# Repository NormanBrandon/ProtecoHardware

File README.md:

# ProtecoHardware
Repositorio Provisional del Proyecto de La sección de Hardware

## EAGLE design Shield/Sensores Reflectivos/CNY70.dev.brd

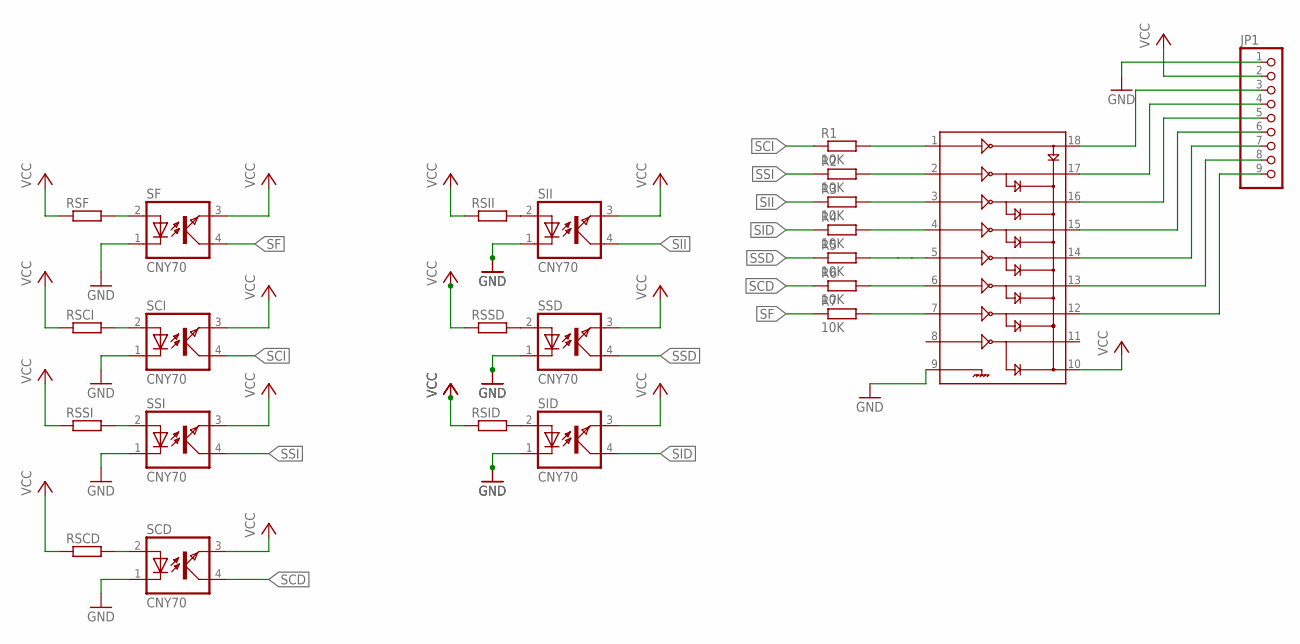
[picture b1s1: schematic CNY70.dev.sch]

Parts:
JP1: PINHD-1X9/90; 1X09/90
R1, R2, R3, R4, R5, R6, R7: 10K; R1206
RSCD: R-EU_R1206; R1206
RSCI: R-EU_R1206; R1206
RSF: R-EU_R1206; R1206
RSID: R-EU_R1206; R1206
RSII: R-EU_R1206; R1206
RSSD: R-EU_R1206; R1206
RSSI: R-EU_R1206; R1206
SCD: CNY70
SCI: CNY70
SF: CNY70
SID: CNY70
SII: CNY70
SSD: CNY70
SSI: CNY70
ULN1: ULN2803; DIL18

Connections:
GND: JP1.1, SCD.1, SCI.1, SF.1, SID.1, SII.1, SSD.1, SSI.1, ULN1.9
unnamed: RSII.2, SII.2
unnamed: RSSD.2, SSD.2
unnamed: RSID.2, SID.2
unnamed: JP1.3, ULN1.18
unnamed: RSCD.2, SCD.2
unnamed: RSSI.2, SSI.2
unnamed: RSCI.2, SCI.2
unnamed: RSF.2, SF.2
unnamed: JP1.4, ULN1.17
unnamed: JP1.5, ULN1.16
unnamed: JP1.6, ULN1.15
unnamed: JP1.7, ULN1.14
unnamed: JP1.8, ULN1.13
unnamed: JP1.9, ULN1.12
unnamed: R1.2, ULN1.1
unnamed: R2.2, ULN1.2
unnamed: R3.2, ULN1.3
unnamed: R4.2, ULN1.4
unnamed: R5.2, ULN1.5
unnamed: R6.2, ULN1.6
unnamed: R7.2, ULN1.7
SCD: R6.1, SCD.4
SCI: R1.1, SCI.4
SF: R7.1, SF.4
SID: R4.1, SID.4
SII: R3.1, SII.4
SSD: R5.1, SSD.4
SSI: R2.1, SSI.4
VCC: JP1.2, RSCD.1, RSCI.1, RSF.1, RSID.1, RSII.1, RSSD.1, RSSI.1, SCD.3, SCI.3, SF.3, SID.3, SII.3, SSD.3, SSI.3, ULN1.10

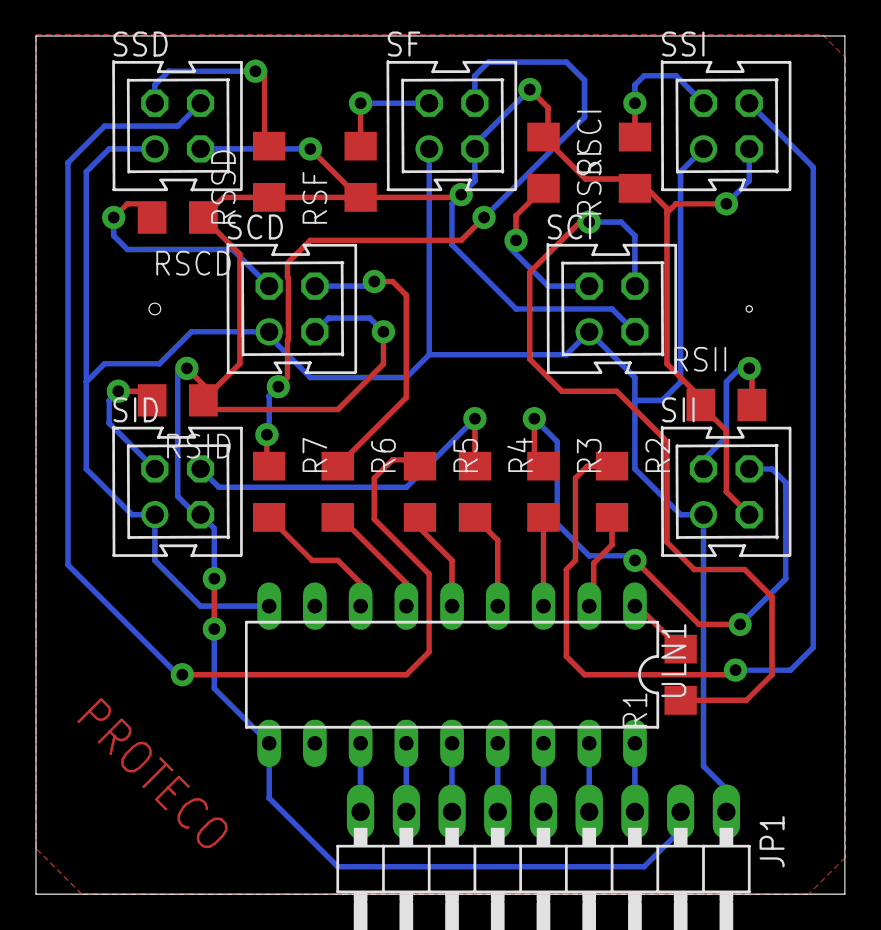
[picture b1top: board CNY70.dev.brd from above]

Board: 2 copper layers, 44.9 x 47.7 mm, 23 parts (0 on the bottom side), 30 nets.

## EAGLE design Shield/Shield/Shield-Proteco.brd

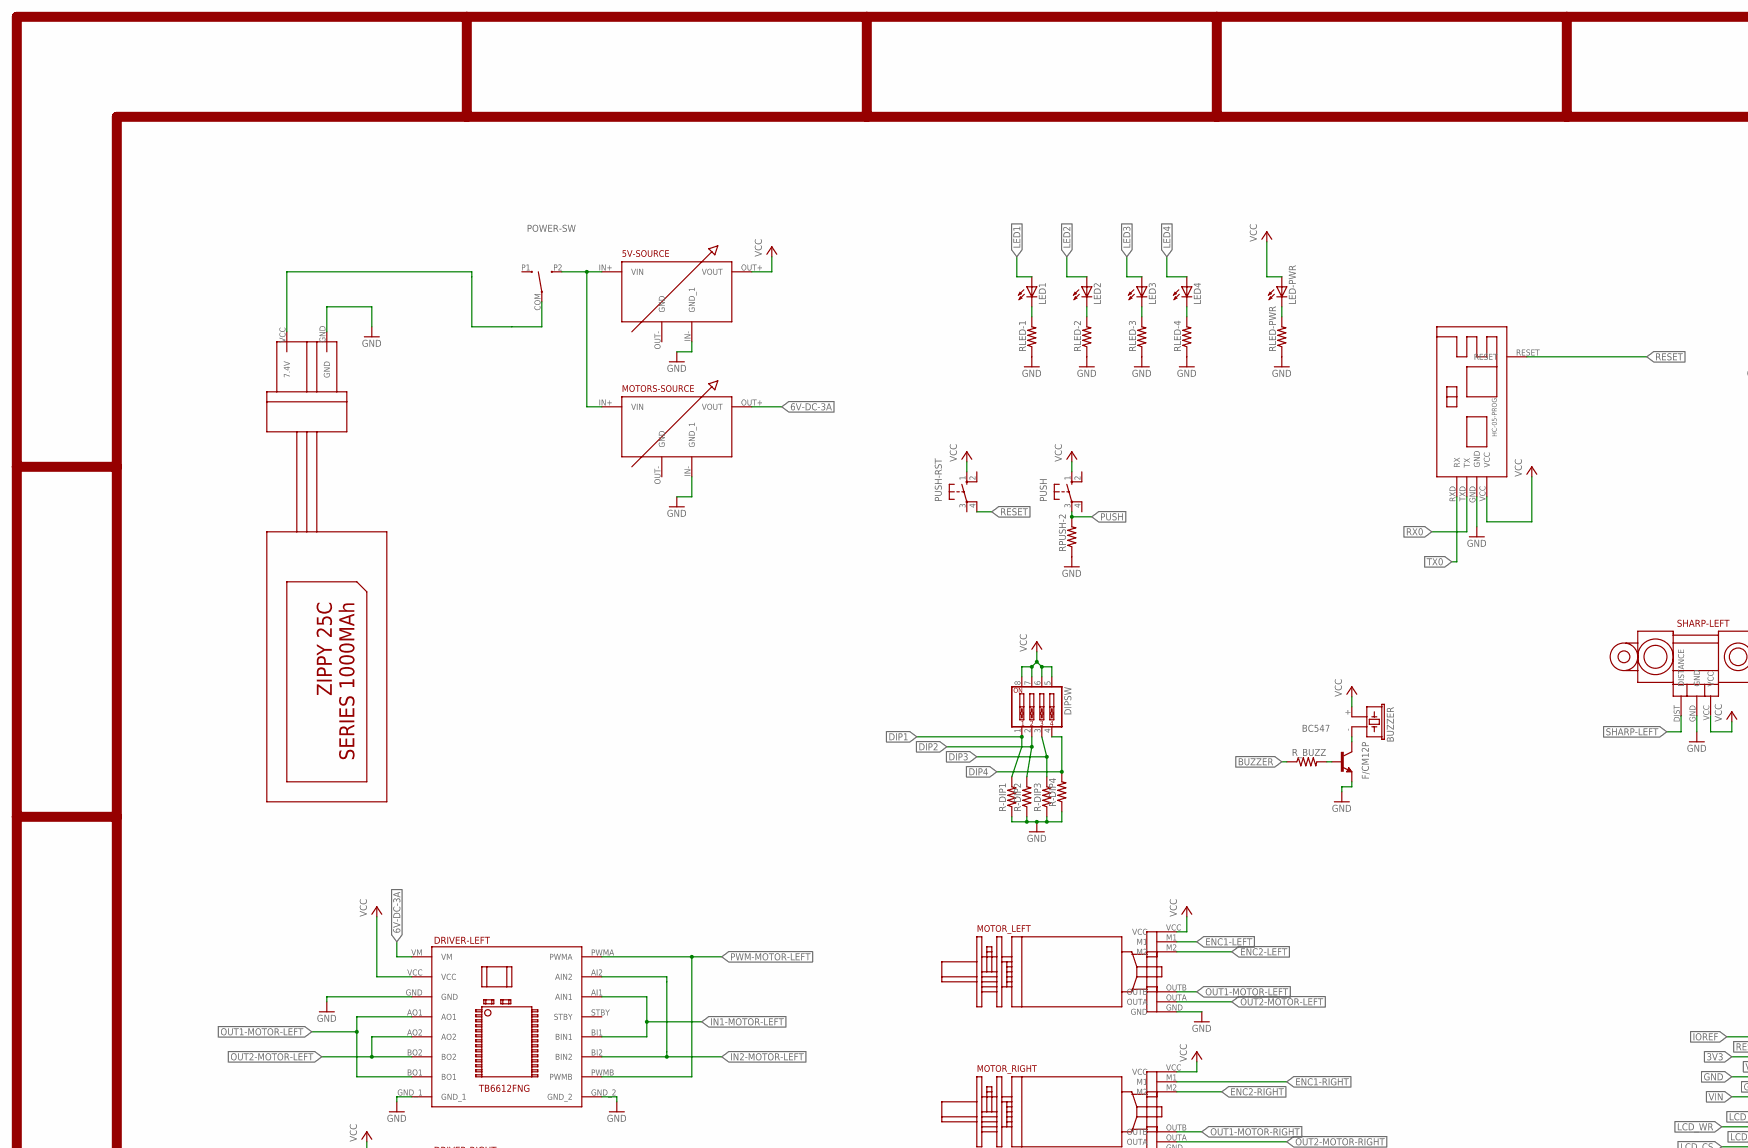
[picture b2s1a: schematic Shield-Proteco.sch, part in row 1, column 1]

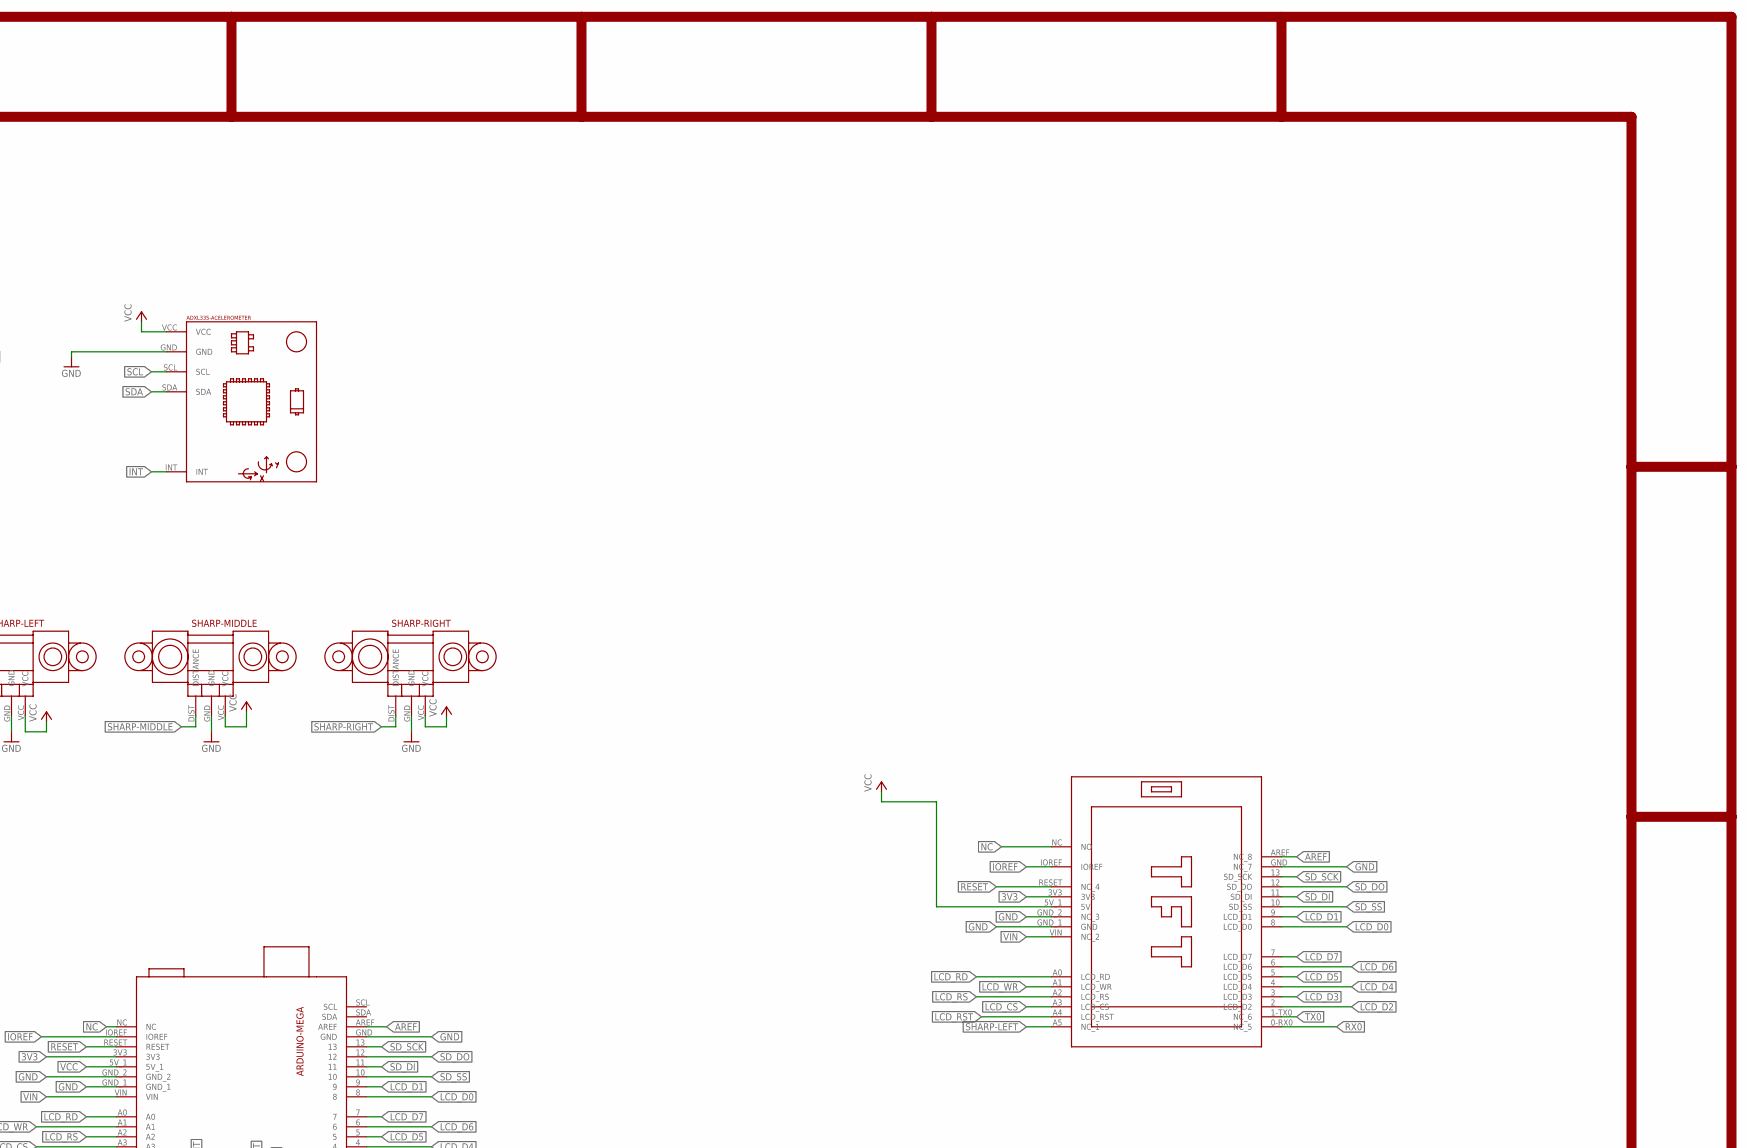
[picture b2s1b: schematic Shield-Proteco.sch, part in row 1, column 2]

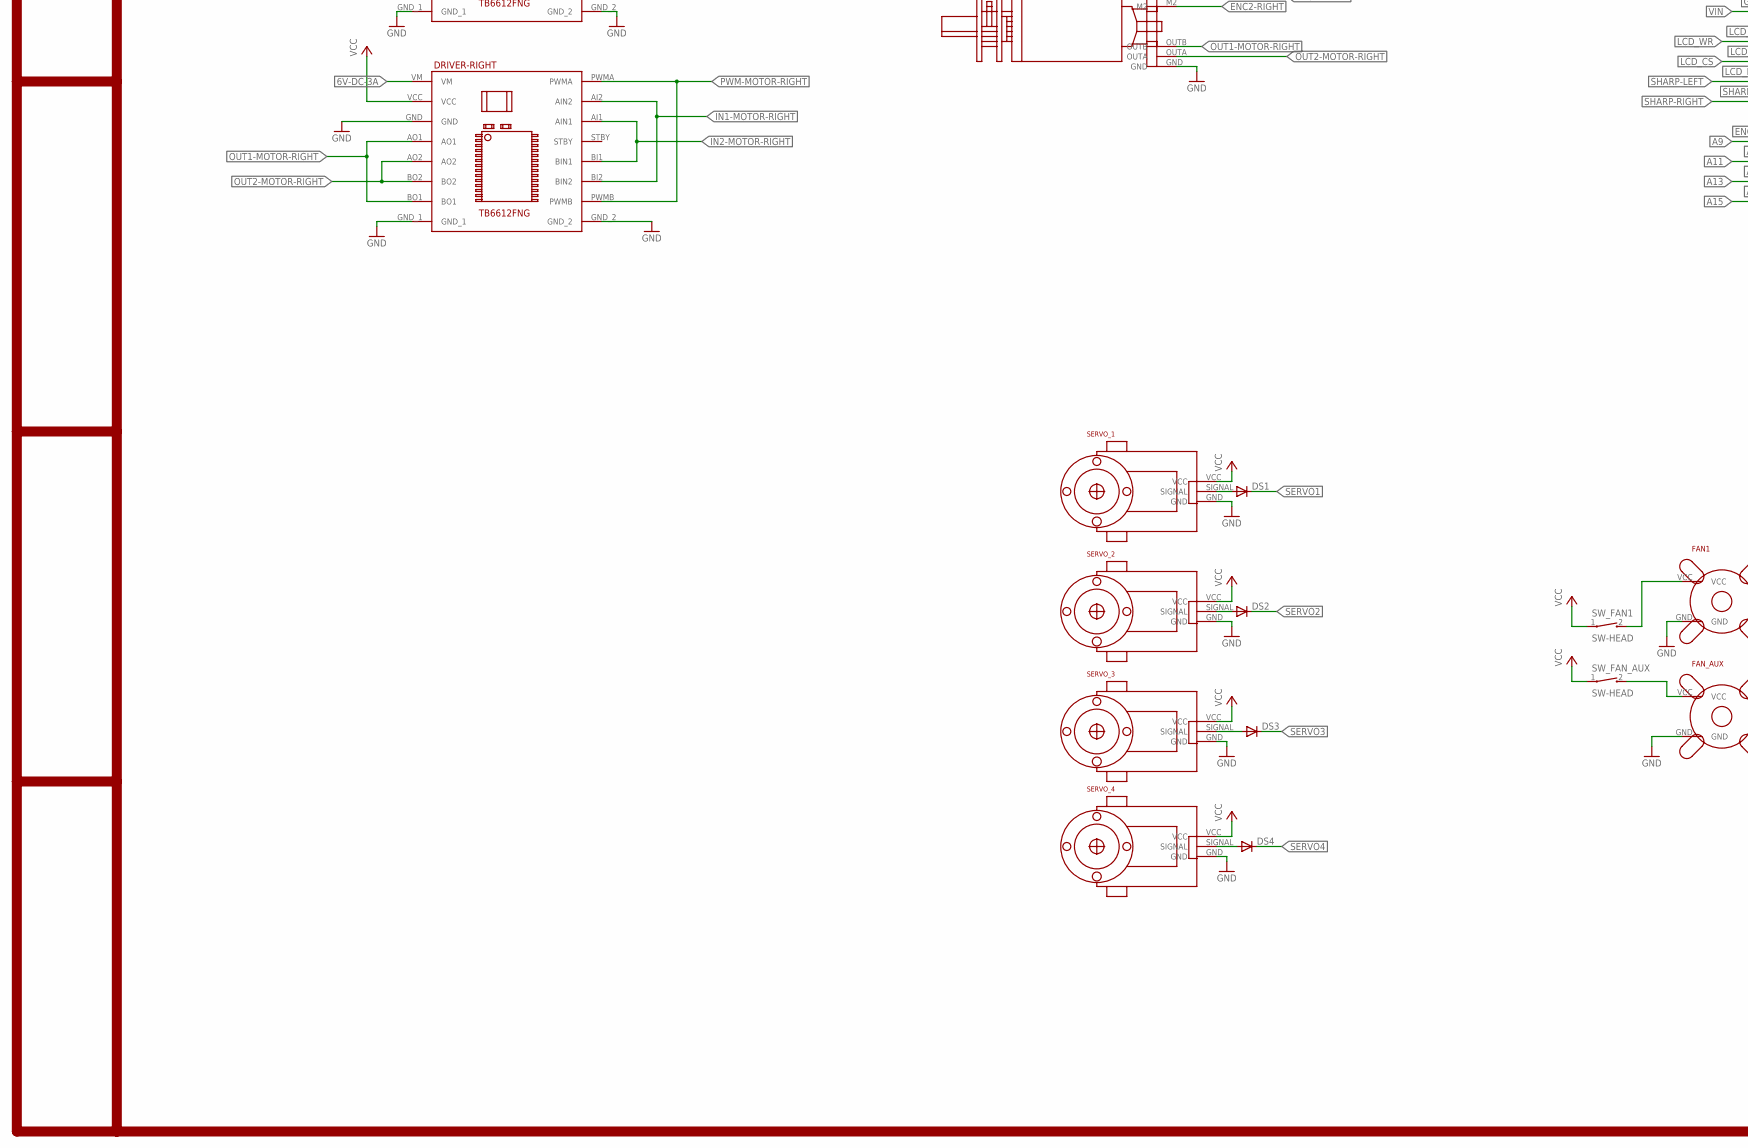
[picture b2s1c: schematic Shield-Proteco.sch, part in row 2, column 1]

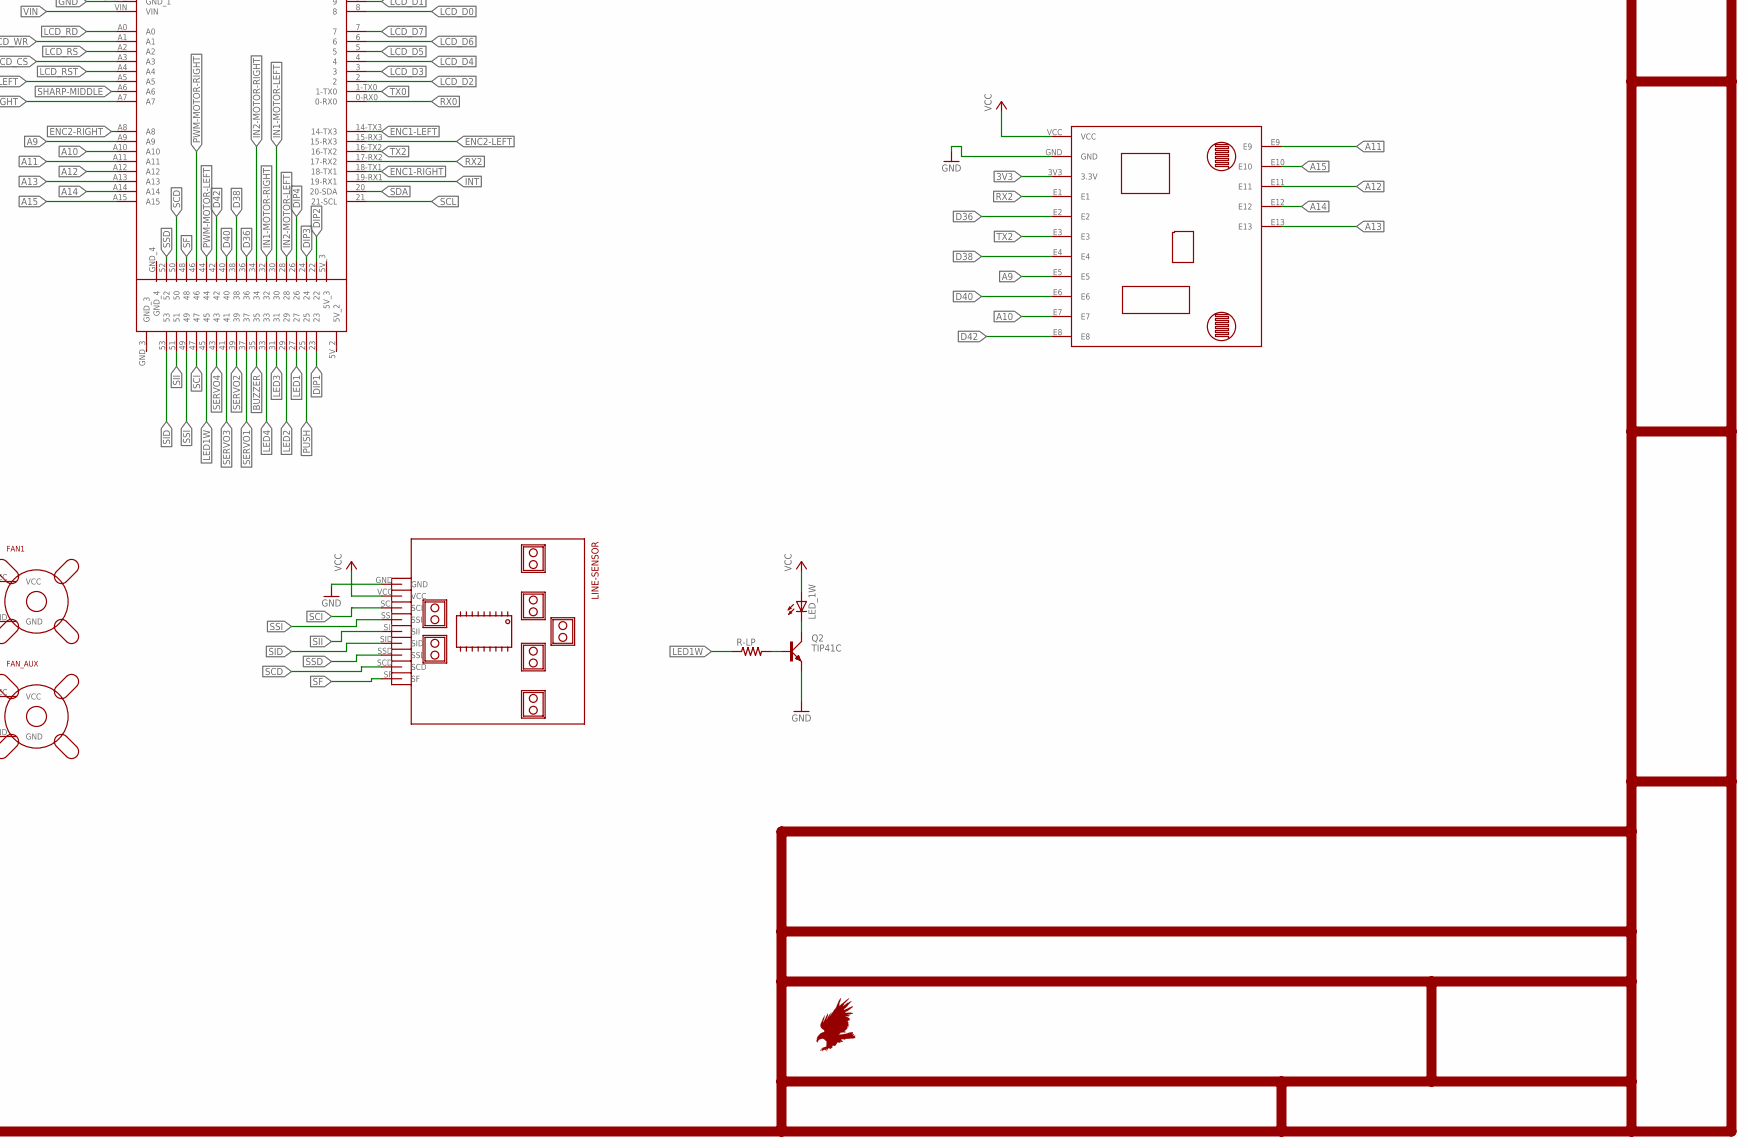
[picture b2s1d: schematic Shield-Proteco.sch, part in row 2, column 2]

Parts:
5V-SOURCE: STEPDOWN-DC-DC
ADXL335-ACELEROMETER: ACELEROMETER-JST-5; ACELEROMETER-MPU6050-JST-5
ARDUINO-MEGA: ARDUINO_MEGA; ARDUINO-MEGA
BC547: BC547-NPN-TO92-CBE; TO92-CBE
BUZZER: F/CM12P
DIPSW: SW_DIP-4; EDG-04
DRIVER-LEFT: TB6612FNG
DRIVER-RIGHT: TB6612FNG
DS1, DS2, DS3, DS4: DIODE-DO-214AC; DO-214AC
FAN1: FAN-MOLEX; 1X02
FAN_AUX: FAN-MOLEX; 1X02
HC-05-PROG: HC-05-PROGRAMER; HC-05-PROG-COMP
LED1, LED2, LED3, LED4: LEDCHIPLED_1206; CHIPLED_1206
LED-PWR: LEDCHIPLED_1206; CHIPLED_1206
LED_1W: LED-1W-3V3; 1X02
LINE-SENSOR: CNY70-ARRAY-HEADER
MOTORS-SOURCE: STEPDOWN-DC-DC
MOTOR_LEFT: POLOLU-MICROMOTOR; JST
MOTOR_RIGHT: POLOLU-MICROMOTOR; JST
POWER-SW: SLIDE-3
PUSH: 10-XX; B3F-10XX
PUSH-RST: 10-XX; B3F-10XX
Q2: TIP41C; TO220AV
R-DIP1, R-DIP2, R-DIP3, R-DIP4: R-US_M1206; M1206
R-LP: R-US_M1206; M1206
RLED-1, RLED-2, RLED-3, RLED-4: R-US_M1206; M1206
RLED-PWR: R-US_M1206; M1206
RPUSH-2: R-US_M1206; M1206
R_BUZZ: R-US_M1206; M1206
SERVO_1, SERVO_2, SERVO_3, SERVO_4: SERVOMOTORES; SERVO
SHARP-LEFT: SHARP
SHARP-MIDDLE: SHARP
SHARP-RIGHT: SHARP
SW_FAN1: SW-HEAD; 1X02
SW_FAN_AUX: SW-HEAD; 1X02
U$9: SENSOR-MISCELANEOUS
U$14: TFT_ARDUINO-UNO-MEGA; TFT-ARDUINO-UNO-MEGA
U$23: ZIIPY-7.4V; XT60

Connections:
3V3: ARDUINO-MEGA.3V3, U$9.3V3 (3.3V), U$14.3V3
6V-DC-3A: DRIVER-LEFT.VM, DRIVER-RIGHT.VM, MOTORS-SOURCE.OUT+ (VOUT)
A9: ARDUINO-MEGA.A9, U$9.E5
A10: ARDUINO-MEGA.A10, U$9.E7
A11: ARDUINO-MEGA.A11, U$9.E9
A12: ARDUINO-MEGA.A12, U$9.E11
A13: ARDUINO-MEGA.A13, U$9.E13
A14: ARDUINO-MEGA.A14, U$9.E12
A15: ARDUINO-MEGA.A15, U$9.E10
AREF: ARDUINO-MEGA.AREF, U$14.AREF (NC_8)
BUZZER: ARDUINO-MEGA.35, R_BUZZ.1
D36: ARDUINO-MEGA.36, U$9.E2
D38: ARDUINO-MEGA.38, U$9.E4
D40: ARDUINO-MEGA.40, U$9.E6
D42: ARDUINO-MEGA.42, U$9.E8
DIP1: ARDUINO-MEGA.23, DIPSW.1, R-DIP1.2
DIP2: ARDUINO-MEGA.22, DIPSW.2, R-DIP2.2
ENC1-LEFT: ARDUINO-MEGA.14-TX3, MOTOR_LEFT.M1
ENC1-RIGHT: ARDUINO-MEGA.18-TX1, MOTOR_RIGHT.M1
ENC2-LEFT: ARDUINO-MEGA.15-RX3, MOTOR_LEFT.M2
ENC2-RIGHT: ARDUINO-MEGA.A8, MOTOR_RIGHT.M2
GND: 5V-SOURCE.IN- (GND_1), ADXL335-ACELEROMETER.GND, ARDUINO-MEGA.GND, ARDUINO-MEGA.GND_1, ARDUINO-MEGA.GND_2, BC547.E, DRIVER-LEFT.GND, DRIVER-LEFT.GND_1, DRIVER-LEFT.GND_2, DRIVER-RIGHT.GND, DRIVER-RIGHT.GND_1, DRIVER-RIGHT.GND_2, FAN1.GND, FAN_AUX.GND, HC-05-PROG.GND, LINE-SENSOR.GND, MOTORS-SOURCE.IN- (GND_1), MOTOR_LEFT.GND, MOTOR_RIGHT.GND, Q2.E, R-DIP1.1, R-DIP2.1, R-DIP3.1, R-DIP4.1, RLED-1.1, RLED-2.1, RLED-3.1, RLED-4.1, RLED-PWR.1, RPUSH-2.1, SERVO_1.GND, SERVO_2.GND, SERVO_3.GND, SERVO_4.GND, SHARP-LEFT.GND, SHARP-MIDDLE.GND, SHARP-RIGHT.GND, U$9.GND, U$14.GND (NC_7), U$14.GND_1 (GND), U$14.GND_2 (NC_3), U$23.GND; also elsewhere on the board
IN1-MOTOR-LEFT: ARDUINO-MEGA.30, DRIVER-LEFT.AI1 (AIN1), DRIVER-LEFT.BI1 (BIN1)
IN1-MOTOR-RIGHT: ARDUINO-MEGA.32, DRIVER-RIGHT.AI2 (AIN2), DRIVER-RIGHT.BI2 (BIN2)
IN2-MOTOR-LEFT: ARDUINO-MEGA.28, DRIVER-LEFT.AI2 (AIN2), DRIVER-LEFT.BI2 (BIN2)
IN2-MOTOR-RIGHT: ARDUINO-MEGA.34, DRIVER-RIGHT.AI1 (AIN1), DRIVER-RIGHT.BI1 (BIN1)
INT: ADXL335-ACELEROMETER.INT, ARDUINO-MEGA.19-RX1
IOREF: ARDUINO-MEGA.IOREF, U$14.IOREF
LCD_CS: ARDUINO-MEGA.A3, U$14.A3 (LCD_CS)
LCD_D0: ARDUINO-MEGA.8, U$14.8 (LCD_D0)
LCD_D1: ARDUINO-MEGA.9, U$14.9 (LCD_D1)
LCD_D2: ARDUINO-MEGA.2, U$14.2 (LCD_D2)
LCD_D3: ARDUINO-MEGA.3, U$14.3 (LCD_D3)
LCD_D4: ARDUINO-MEGA.4, U$14.4 (LCD_D4)
LCD_D5: ARDUINO-MEGA.5, U$14.5 (LCD_D5)
LCD_D6: ARDUINO-MEGA.6, U$14.6 (LCD_D6)
LCD_D7: ARDUINO-MEGA.7, U$14.7 (LCD_D7)
LCD_RD: ARDUINO-MEGA.A0, U$14.A0 (LCD_RD)
LCD_RS: ARDUINO-MEGA.A2, U$14.A2 (LCD_RS)
LCD_RST: ARDUINO-MEGA.A4, U$14.A4 (LCD_RST)
LCD_WR: ARDUINO-MEGA.A1, U$14.A1 (LCD_WR)
LED1: ARDUINO-MEGA.27, LED1.A
LED1W: ARDUINO-MEGA.45, R-LP.1
LED2: ARDUINO-MEGA.29, LED2.A
LED3: ARDUINO-MEGA.31, LED3.A
LED4: ARDUINO-MEGA.33, LED4.A
unnamed: LED_1W.2 (C), Q2.C
unnamed: Q2.B, R-LP.2
unnamed: BC547.C, BUZZER.- (2)
unnamed: BC547.B, R_BUZZ.2
unnamed: FAN_AUX.VCC, SW_FAN_AUX.2
unnamed: LED1.C, RLED-1.2
unnamed: LED2.C, RLED-2.2
unnamed: LED3.C, RLED-3.2
unnamed: LED4.C, RLED-4.2
unnamed: DS4.A, SERVO_4.SIGNAL
unnamed: DS3.A, SERVO_3.SIGNAL
unnamed: DS2.A, SERVO_2.SIGNAL
unnamed: LED-PWR.C, RLED-PWR.2
unnamed: DS1.A, SERVO_1.SIGNAL
unnamed: FAN1.VCC, SW_FAN1.2
unnamed 102: POWER-SW.COM, U$23.VCC (7.4V); also elsewhere on the board
NC: ARDUINO-MEGA.NC, U$14.NC (NO)
OUT1-MOTOR-LEFT: DRIVER-LEFT.AO1, DRIVER-LEFT.BO1, MOTOR_LEFT.OUTB
OUT1-MOTOR-RIGHT: DRIVER-RIGHT.AO1, DRIVER-RIGHT.BO1, MOTOR_RIGHT.OUTB
OUT2-MOTOR-LEFT: DRIVER-LEFT.AO2, DRIVER-LEFT.BO2, MOTOR_LEFT.OUTA
OUT2-MOTOR-RIGHT: DRIVER-RIGHT.AO2, DRIVER-RIGHT.BO2, MOTOR_RIGHT.OUTA
PUSH: ARDUINO-MEGA.25, PUSH.3, RPUSH-2.2
PWM-MOTOR-LEFT: ARDUINO-MEGA.44, DRIVER-LEFT.PWMA, DRIVER-LEFT.PWMB
PWM-MOTOR-RIGHT: ARDUINO-MEGA.46, DRIVER-RIGHT.PWMA, DRIVER-RIGHT.PWMB
RESET: ARDUINO-MEGA.RESET, HC-05-PROG.RESET, PUSH-RST.4 (P1), U$14.RESET (NC_4)
RX0: ARDUINO-MEGA.0-RX0, HC-05-PROG.TXD (TX), U$14.0-RX0 (NC_5)
RX2: ARDUINO-MEGA.17-RX2, U$9.E1
SCD: ARDUINO-MEGA.50, LINE-SENSOR.SCD
SCI: ARDUINO-MEGA.47, LINE-SENSOR.SCI
SCL: ADXL335-ACELEROMETER.SCL, ARDUINO-MEGA.21 (21-SCL)
SDA: ADXL335-ACELEROMETER.SDA, ARDUINO-MEGA.20 (20-SDA)
SD_DI: ARDUINO-MEGA.11, U$14.11 (SD_DI)
SD_DO: ARDUINO-MEGA.12, U$14.12 (SD_DO)
SD_SCK: ARDUINO-MEGA.13, U$14.13 (SD_SCK)
SD_SS: ARDUINO-MEGA.10, U$14.10 (SD_SS)
SERVO1: ARDUINO-MEGA.37, DS1.C
SERVO2: ARDUINO-MEGA.39, DS2.C
SERVO3: ARDUINO-MEGA.41, DS3.C
SERVO4: ARDUINO-MEGA.43, DS4.C
SF: ARDUINO-MEGA.48, LINE-SENSOR.SF
SHARP-LEFT: ARDUINO-MEGA.A5, SHARP-LEFT.DIST (DISTANCE), U$14.A5 (NC_1)
SHARP-MIDDLE: ARDUINO-MEGA.A6, SHARP-MIDDLE.DIST (DISTANCE)
SHARP-RIGHT: ARDUINO-MEGA.A7, SHARP-RIGHT.DIST (DISTANCE)
SID: ARDUINO-MEGA.53, LINE-SENSOR.SID
SII: ARDUINO-MEGA.51, LINE-SENSOR.SII
SSD: ARDUINO-MEGA.52, LINE-SENSOR.SSD
SSI: ARDUINO-MEGA.49, LINE-SENSOR.SSI
TX0: ARDUINO-MEGA.1-TX0, HC-05-PROG.RXD (RX), U$14.1-TX0 (NC_6)
TX2: ARDUINO-MEGA.16-TX2, U$9.E3
VCC: 5V-SOURCE.OUT+ (VOUT), ADXL335-ACELEROMETER.VCC, ARDUINO-MEGA.5V_1, BUZZER.+ (1), DIPSW.5, DIPSW.6, DIPSW.7, DIPSW.8, DRIVER-LEFT.STBY, DRIVER-LEFT.VCC, DRIVER-RIGHT.STBY, DRIVER-RIGHT.VCC, HC-05-PROG.VCC, LED-PWR.A, LED_1W.1 (A), LINE-SENSOR.VCC, MOTOR_LEFT.VCC, MOTOR_RIGHT.VCC, PUSH.1 (S), PUSH-RST.1 (S), SERVO_1.VCC, SERVO_2.VCC, SERVO_3.VCC, SERVO_4.VCC, SHARP-LEFT.VCC, SHARP-MIDDLE.VCC, SHARP-RIGHT.VCC, SW_FAN1.1, SW_FAN_AUX.1, U$9.VCC, U$14.5V_1 (5V); also elsewhere on the board

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
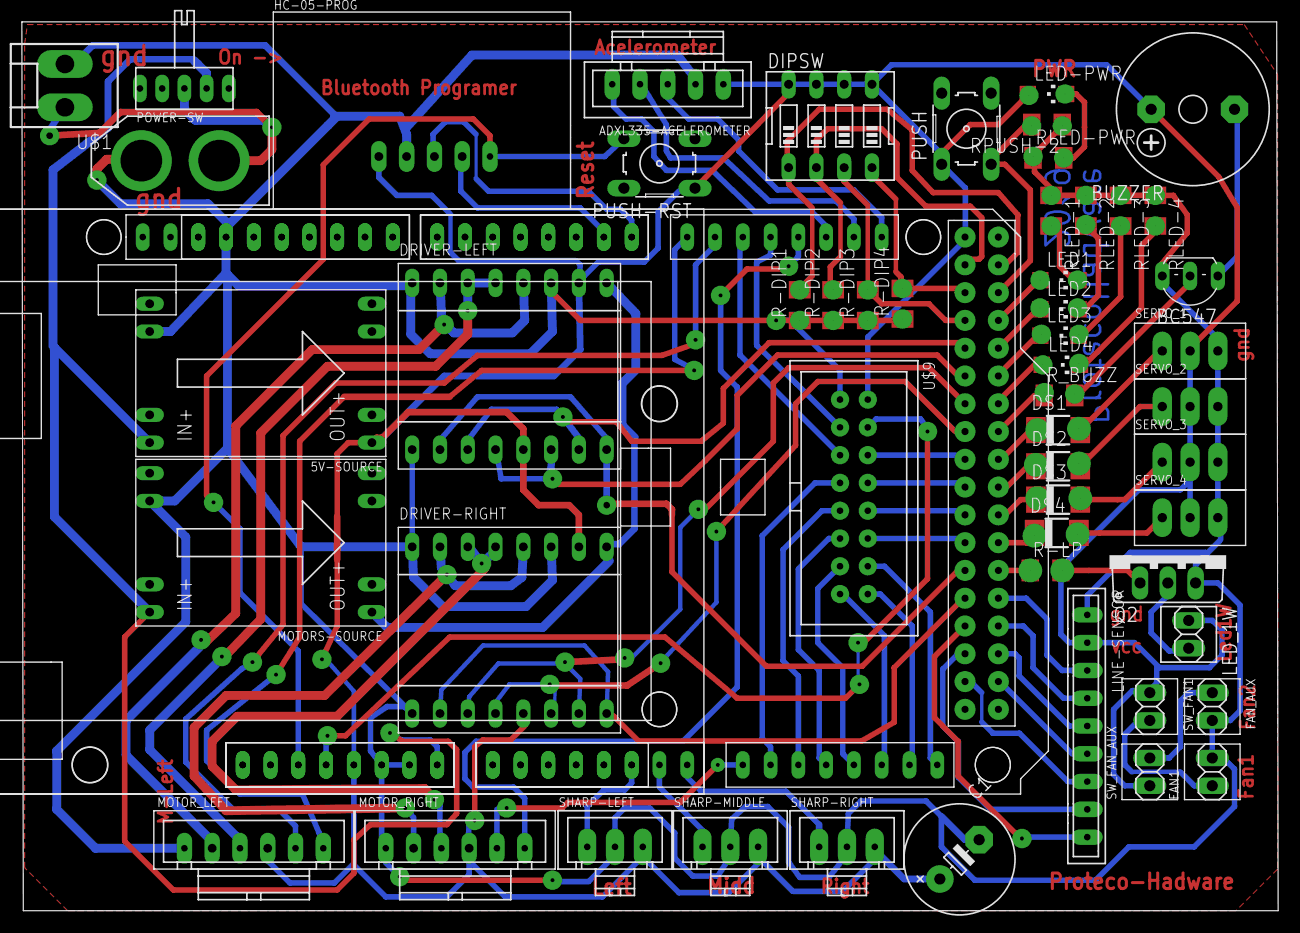
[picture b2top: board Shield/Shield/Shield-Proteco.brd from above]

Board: 2 copper layers, 114.9 x 81.3 mm, 55 parts (0 on the bottom side), 99 nets.

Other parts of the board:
C1: E5-10,5
U$1: LIPO7.4MOLEX; KK-156-2

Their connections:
GND: C1.-, U$1.GND; also elsewhere on the board
unnamed 102: U$1.VCC; also elsewhere on the board
VCC: C1.+; also elsewhere on the board

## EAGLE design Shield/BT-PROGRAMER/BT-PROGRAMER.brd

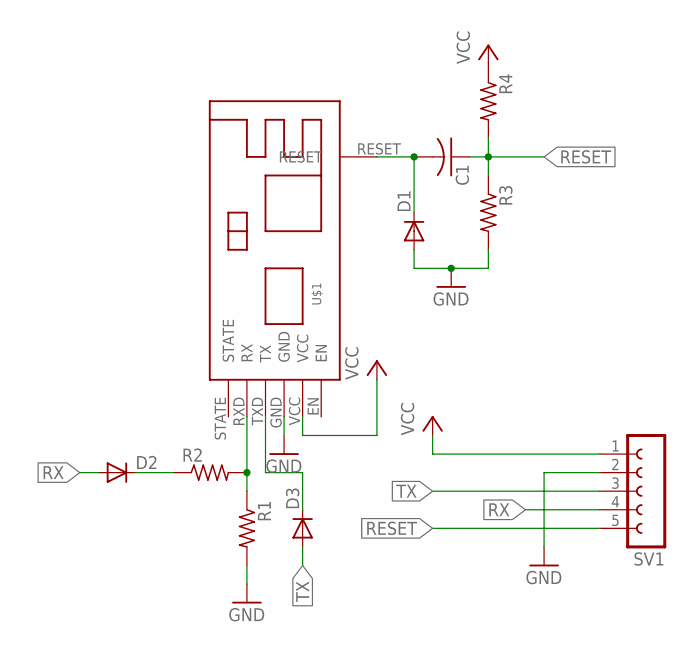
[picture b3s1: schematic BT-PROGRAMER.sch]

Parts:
C1: C-USC0603; C0603
D1, D2, D3: DIODE-DO-214AC; DO-214AC
R1, R2, R3, R4: R-US_M1206; M1206
SV1: FE05-1
U$1: HC-05-PROG

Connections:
GND: D1.A, R1.2, R3.2, SV1.2, U$1.GND
unnamed: R1.1, R2.2, U$1.RXD (RX)
unnamed: C1.2, D1.C, U$1.RESET
unnamed: D2.C, R2.1
unnamed: D3.C, U$1.TXD (TX)
RESET: C1.1, R3.1, R4.2, SV1.5
RX: D2.A, SV1.4
TX: D3.A, SV1.3
VCC: R4.1, SV1.1, U$1.VCC

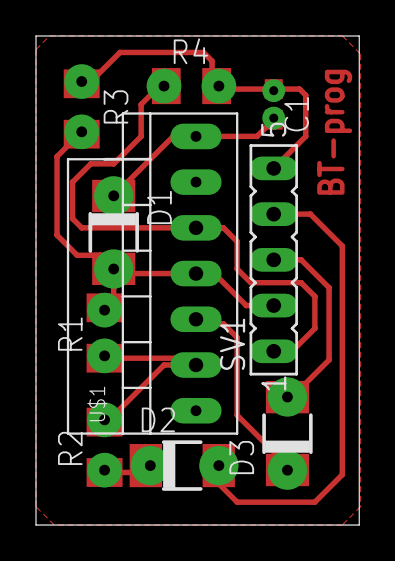
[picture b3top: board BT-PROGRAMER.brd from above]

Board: 2 copper layers, 18.0 x 27.2 mm, 10 parts (0 on the bottom side), 9 nets.

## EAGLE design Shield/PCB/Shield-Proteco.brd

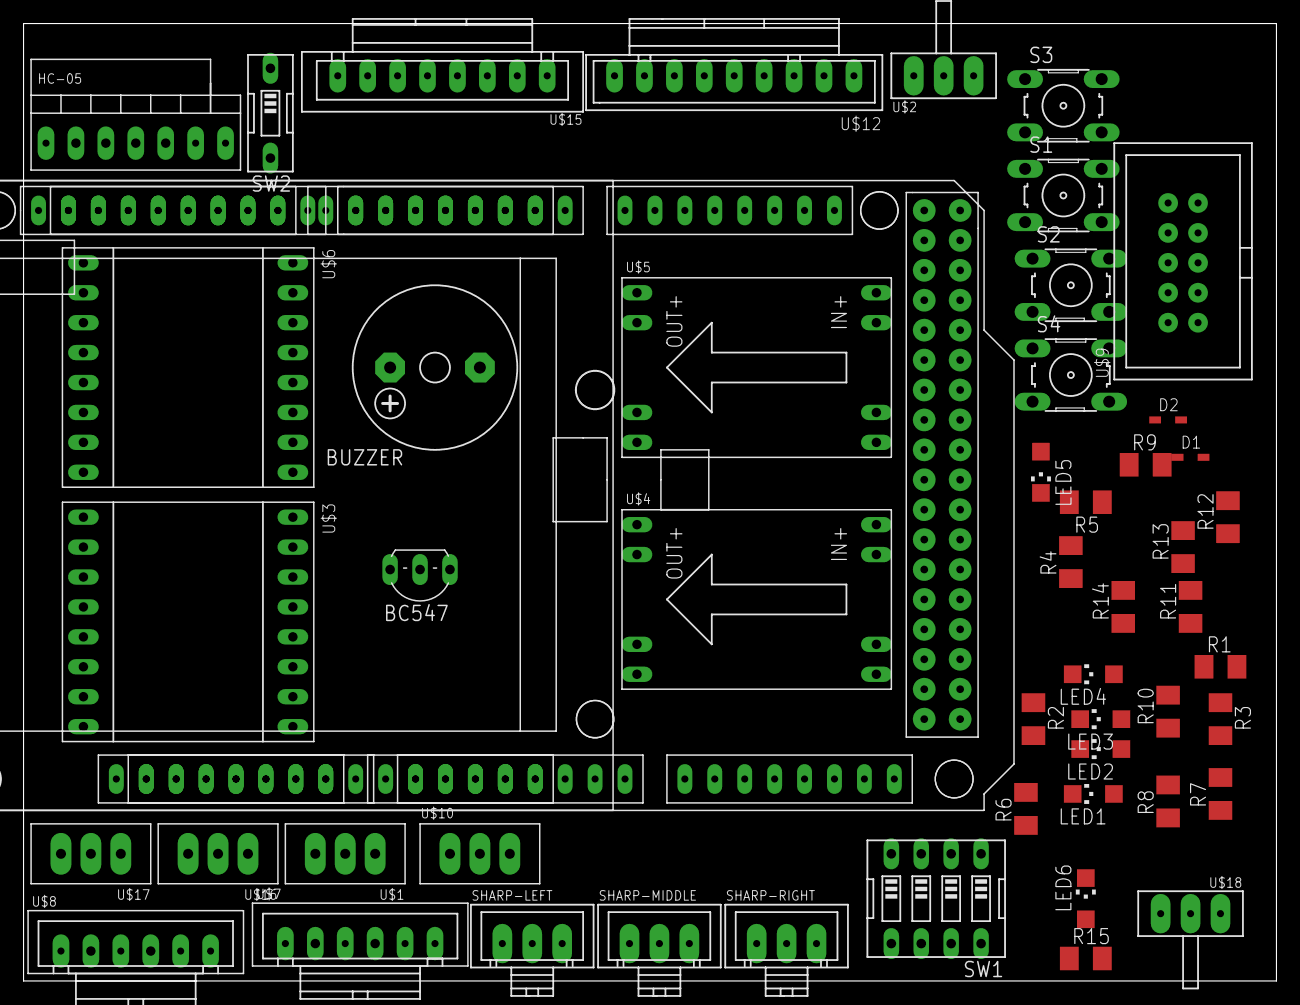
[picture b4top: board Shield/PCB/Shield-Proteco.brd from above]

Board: 2 copper layers, 106.3 x 81.3 mm, 52 parts (0 on the bottom side), 37 nets, no tracks yet.

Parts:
ARDUINO-MEGA: ARDUINO_MEGA; ARDUINO-MEGA
BC547: TO92-CBE
BUZZER: F/CM12P
D1, D2: SOD323
HC-05: HC-05-PROG
LED1, LED2, LED3, LED4, LED5, LED6: CHIPLED_1206
R1, R2, R3, R4, R5, R6, R7, R8, R9, R10, R11, R12, R13, R14, R15: M1206
S1, S2, S3, S4: B3F-10XX
SHARP-LEFT: SHARP
SHARP-MIDDLE: SHARP
SHARP-RIGHT: SHARP
SW1: EDG-04
SW2: EDG-01
U$1, U$10, U$16, U$17: SERVOMOTORES; SERVO
U$2, U$18: SLIDE-3
U$3, U$6: TB6612FNG
U$4, U$5: STEPDOWN-DC-DC
U$7, U$8: POLOLU-MICROMOTOR; JST
U$9: SENSOR-MISCELANEOUS
U$12: CNY70-ARRAY
U$14: TFT_ARDUINO-UNO-MEGA; TFT-ARDUINO-UNO-MEGA
U$15: ACELEROMETER-MPU6050-JST

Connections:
6V-DC-3A: U$3.VM, U$5.OUT+, U$6.VM
GND: BC547.E, HC-05.GND, R1.1, R2.1, R3.1, R4.1, R6.1, R7.1, R8.1, R9.1, R10.1, R11.1, R12.1, R13.1, R14.1, R15.1, SHARP-LEFT.GND, SHARP-MIDDLE.GND, SHARP-RIGHT.GND, U$1.GND, U$3.GND, U$3.GND_1, U$3.GND_2, U$4.IN-, U$4.OUT-, U$5.IN-, U$5.OUT-, U$6.GND, U$6.GND_1, U$6.GND_2, U$7.GND, U$8.GND, U$9.GND, U$10.GND, U$12.GND, U$15.GND, U$16.GND, U$17.GND
unnamed: R1.2, SW1.1
unnamed: R2.2, SW1.2
unnamed: R3.2, SW1.3
unnamed: R4.2, SW1.4
unnamed: BC547.C, BUZZER.-
unnamed: BC547.B, R5.2
unnamed: R7.2, S2.3, S2.4
unnamed: R6.2, S1.3, S1.4
unnamed: R8.2, S3.3, S3.4
unnamed: R9.2, S4.3, S4.4
unnamed: U$2.P2, U$4.IN+, U$5.IN+
unnamed: HC-05.RESET, SW2.1
unnamed: LED1.C, R10.2
unnamed: LED2.C, R11.2
unnamed: LED3.C, R12.2
unnamed: LED4.C, R13.2
unnamed: U$14.5V_1, U$18.P2
unnamed: U$10.SIGNAL, U$17.SIGNAL
unnamed: LED5.C, R14.2
unnamed: LED6.C, R15.2
unnamed: D2.2, HC-05.TXD
unnamed: D1.1, HC-05.RXD
unnamed: U$6.AI1, U$6.BI1
unnamed: U$6.AI2, U$6.BI2
unnamed: U$6.AO2, U$6.BO2
unnamed: U$6.AO1, U$6.BO1
unnamed: U$6.PWMA, U$6.PWMB
unnamed: U$3.AI1, U$3.BI1
unnamed: U$3.AI2, U$3.BI2
unnamed: U$3.PWMA, U$3.PWMB
unnamed: U$3.AO2, U$3.BO2
unnamed: U$3.AO1, U$3.BO1
RESET: ARDUINO-MEGA.RESET, SW2.2, U$14.RESET
SD_SCK: ARDUINO-MEGA.13, U$14.13
VCC: BUZZER.+, HC-05.VCC, LED6.A, S1.1, S2.1, S3.1, S4.1, SHARP-LEFT.VCC, SHARP-MIDDLE.VCC, SHARP-RIGHT.VCC, SW1.5, SW1.6, SW1.7, SW1.8, U$1.VCC, U$3.VCC, U$4.OUT+, U$6.VCC, U$7.VCC, U$8.VCC, U$9.VCC, U$10.VCC, U$12.VCC, U$15.VCC, U$16.VCC, U$17.VCC, U$18.COM

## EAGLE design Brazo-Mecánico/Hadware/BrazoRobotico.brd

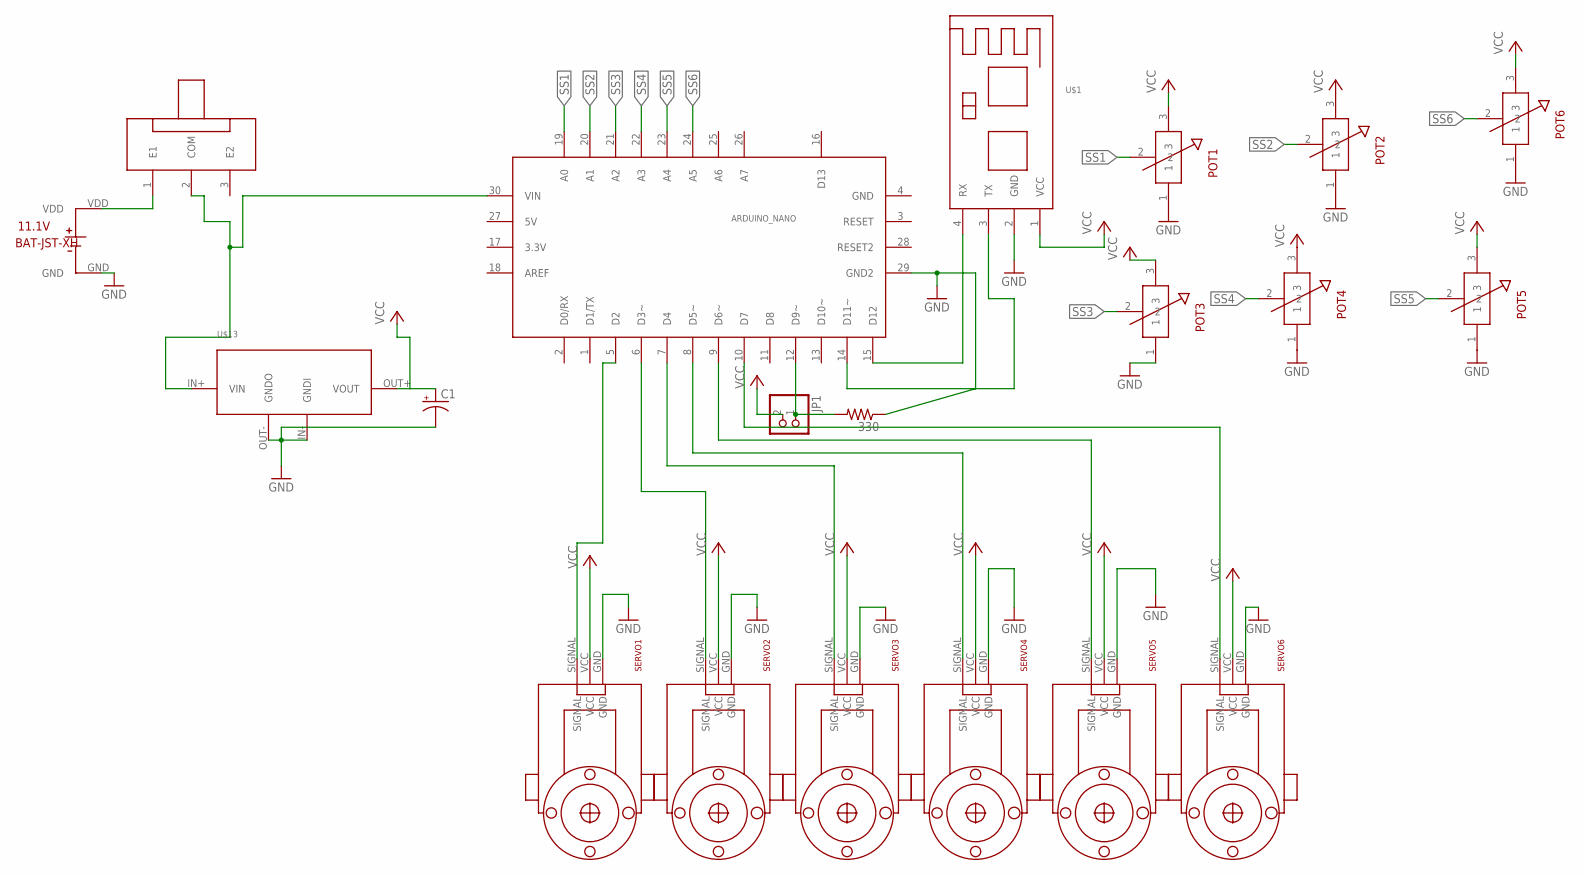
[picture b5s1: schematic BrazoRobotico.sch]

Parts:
11.1V: BAT-JST-XH; JST-XH-2
330: R-US_0207/7; 0207/7
ARDUINO_NANO: NANO
C1: CPOL-USE5-10.5; E5-10,5
JP1: PINHD-1X2; 1X02
POT1, POT2, POT3, POT4, POT5, POT6: POTENCIOMETRO_GDE; POTENCIOMETRO_GENERICO
SERVO1, SERVO2, SERVO3, SERVO4, SERVO5, SERVO6: SERVOMOTORES; SERVO
U$1: HC-06
U$13: STEPDOWN
U$14: TRIPLEPOLO

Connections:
GND: 11.1V.GND, 330.1, ARDUINO_NANO.29 (GND2), C1.-, POT1.1, POT2.1, POT3.1, POT4.1, POT5.1, POT6.1, SERVO1.GND, SERVO2.GND, SERVO3.GND, SERVO4.GND, SERVO5.GND, SERVO6.GND, U$1.2 (GND), U$13.IN- (GNDI), U$13.OUT- (GNDO)
unnamed: ARDUINO_NANO.8 (D5~), SERVO4.SIGNAL
unnamed: ARDUINO_NANO.9 (D6~), SERVO5.SIGNAL
unnamed: ARDUINO_NANO.5 (D2), SERVO1.SIGNAL
unnamed: ARDUINO_NANO.6 (D3~), SERVO2.SIGNAL
unnamed: ARDUINO_NANO.7 (D4), SERVO3.SIGNAL
unnamed: ARDUINO_NANO.30 (VIN), U$13.IN+ (VIN), U$14.2 (COM)
unnamed: ARDUINO_NANO.10 (D7), SERVO6.SIGNAL
unnamed: ARDUINO_NANO.15 (D12), U$1.4 (RX)
unnamed: ARDUINO_NANO.14 (D11~), U$1.3 (TX)
unnamed: 330.2, ARDUINO_NANO.12 (D9~), JP1.1
unnamed: 11.1V.VDD, U$14.1 (E1)
SS1: ARDUINO_NANO.19 (A0), POT1.2
SS2: ARDUINO_NANO.20 (A1), POT2.2
SS3: ARDUINO_NANO.21 (A2), POT3.2
SS4: ARDUINO_NANO.22 (A3), POT4.2
SS5: ARDUINO_NANO.23 (A4), POT5.2
SS6: ARDUINO_NANO.24 (A5), POT6.2
VCC: C1.+, JP1.2, POT1.3, POT2.3, POT3.3, POT4.3, POT5.3, POT6.3, SERVO1.VCC, SERVO2.VCC, SERVO3.VCC, SERVO4.VCC, SERVO5.VCC, SERVO6.VCC, U$1.1 (VCC), U$13.OUT+ (VOUT)

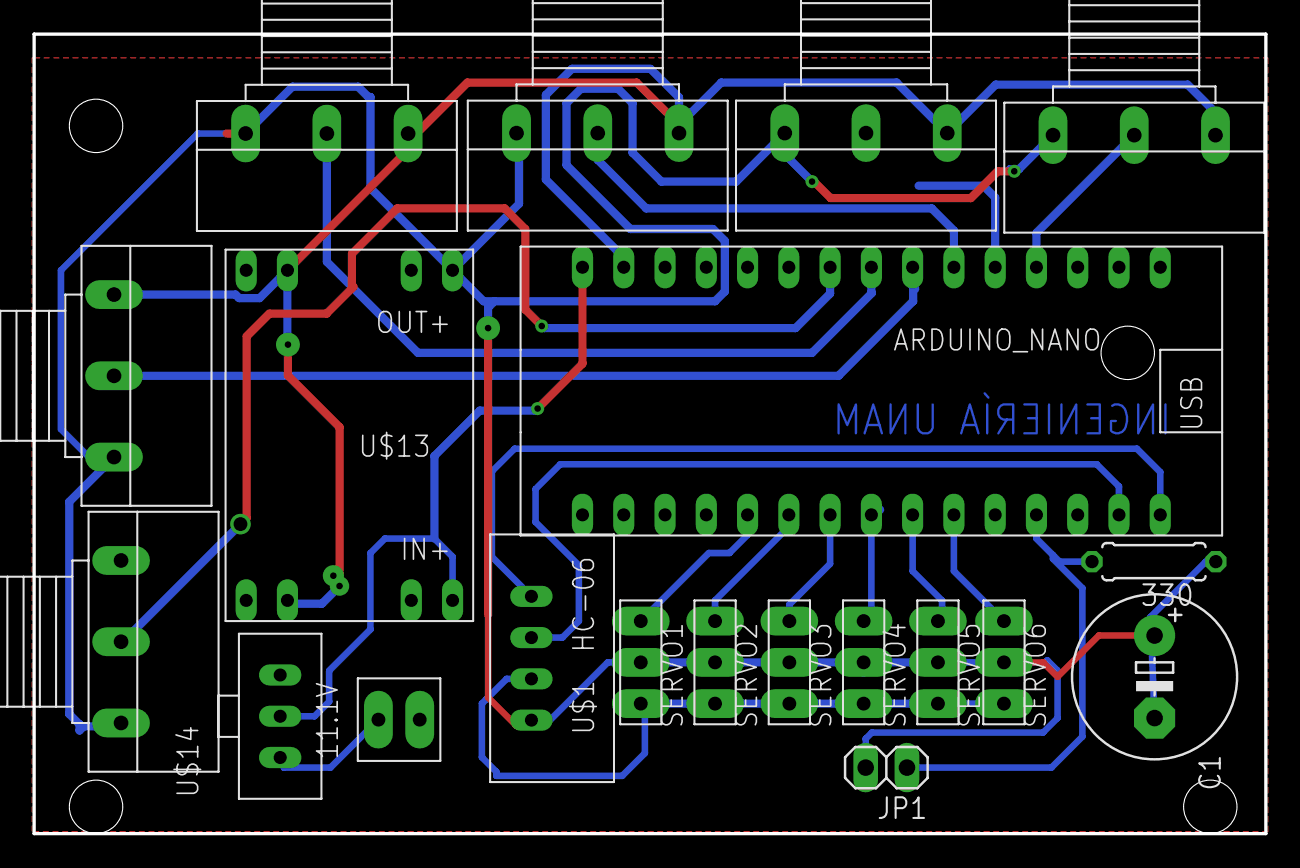
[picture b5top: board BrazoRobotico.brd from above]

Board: 2 copper layers, 75.8 x 49.2 mm, 20 parts (0 on the bottom side), 19 nets.
